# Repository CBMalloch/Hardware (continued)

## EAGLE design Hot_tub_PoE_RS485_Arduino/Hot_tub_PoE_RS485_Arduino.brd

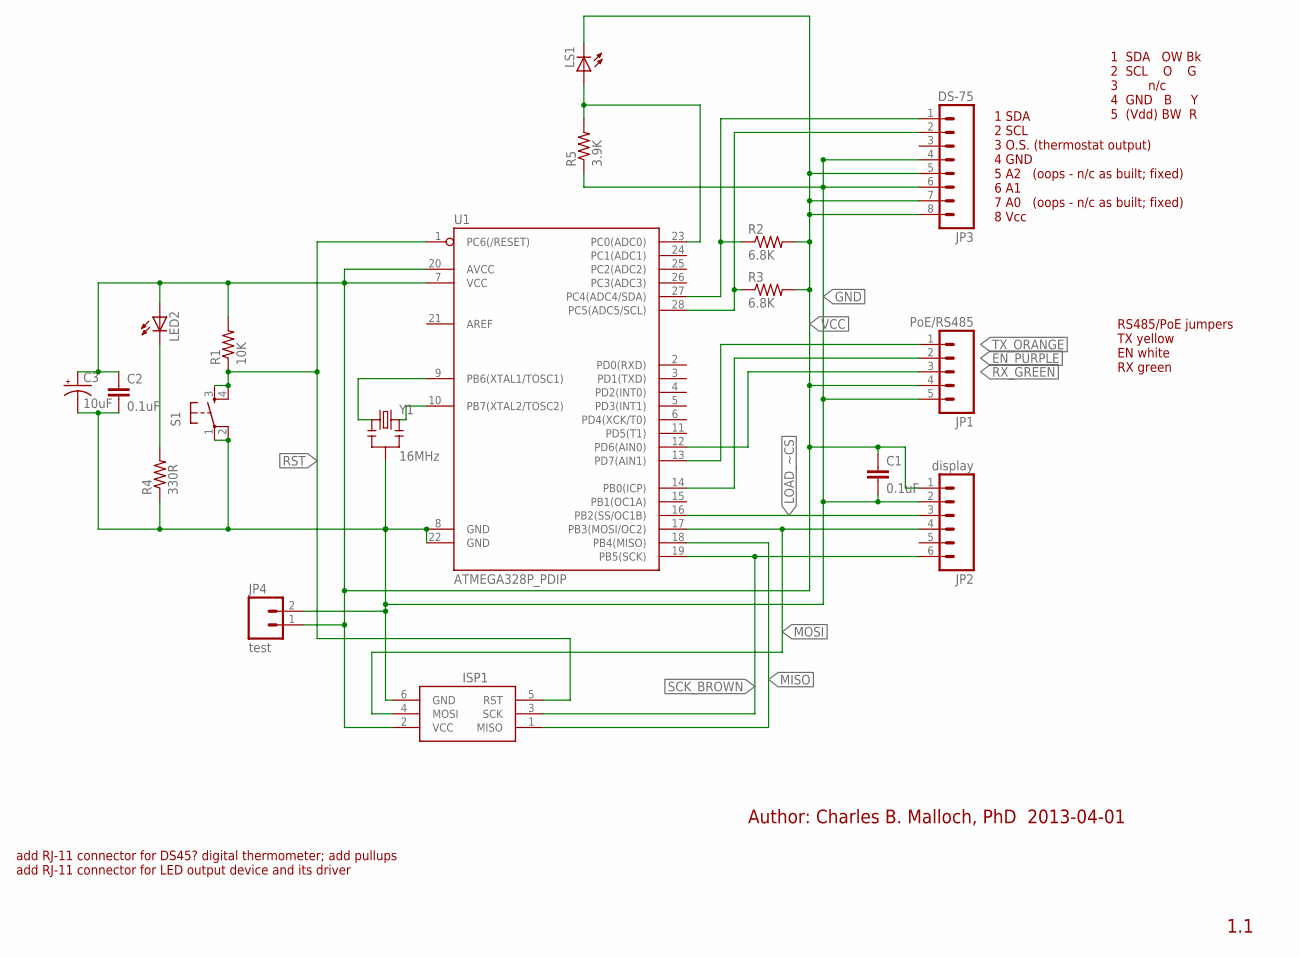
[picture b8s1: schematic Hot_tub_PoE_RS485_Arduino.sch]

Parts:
C1, C2: 0.1uF; CAP-PTH-SMALL
C3: 10uF; CPOL-RADIAL-10UF-25V
ISP1: AVRISP-6; AVRISP
JP1: PoE/RS485; 1X05_LOCK_LONGPADS
JP2: display; 1X06_LOCK_LONGPADS
JP3: DS-75; 1X08_LOCK_LONGPADS
JP4: test; 1X02_LOCK_LONGPADS
LED2: LED5MM
LS1: LED5MM
R1: 10K; 0204/5
R2, R3: 6.8K; 0207/10
R4: 330R; 0207/10
R5: 3.9K; 0207/10
S1: TAC_SWITCHPTH; TACTILE-PTH
U1: ATMEGA328P_PDIP; DIL28-3
Y1: 16MHz; RESONATOR-PTH

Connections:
EN_PURPLE: JP1.2, U1.14 (PB0(ICP))
GND: C1.2, C2.2, C3.2 (-), ISP1.6 (GND), JP1.5, JP2.2, JP3.4, JP3.6, JP4.2, R4.1, R5.1, S1.1, S1.2, U1.8 (GND), U1.22 (GND), Y1.2
LOAD_~CS: JP2.3, U1.16 (PB2(SS/OC1B))
MISO: ISP1.1 (MISO), U1.18 (PB4(MISO))
MOSI: ISP1.4 (MOSI), JP2.4, U1.17 (PB3(MOSI/OC2))
unnamed: JP3.1, R2.1, U1.27 (PC4(ADC4/SDA))
unnamed: LED2.K (C), R4.2
unnamed: LS1.A, R5.2, U1.23 (PC0(ADC0))
unnamed: U1.10 (PB7(XTAL2/TOSC2)), Y1.3
unnamed: JP3.2, R3.1, U1.28 (PC5(ADC5/SCL))
unnamed: U1.9 (PB6(XTAL1/TOSC1)), Y1.1
RST: ISP1.5 (RST), R1.1, S1.3, S1.4, U1.1 (PC6(/RESET))
RX_GREEN: JP1.3, U1.12 (PD6(AIN0))
SCK_BROWN: ISP1.3 (SCK), JP2.6, U1.19 (PB5(SCK))
TX_ORANGE: JP1.1, U1.13 (PD7(AIN1))
VCC: C1.1, C2.1, C3.1 (+), ISP1.2 (VCC), JP1.4, JP2.1, JP3.5, JP3.7, JP3.8, JP4.1, LED2.A, LS1.K (C), R1.2, R2.2, R3.2, U1.7 (VCC), U1.20 (AVCC)

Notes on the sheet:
Author: Charles B. Malloch, PhD 2013-04-01
1.1
add RJ-11 connector for DS45? digital thermometer; add pullups add RJ-11 connector for LED output device and its driver
1 SDA 2 SCL 3 O.S. (thermostat output) 4 GND 5 A2 (oops - n/c as built; fixed) 6 A1 7 A0 (oops - n/c as built; fixed) 8 Vcc
1 SDA OW Bk 2 SCL O G 3 n/c 4 GND B Y 5 (Vdd) BW R
RS485/PoE jumpers TX yellow EN white RX green

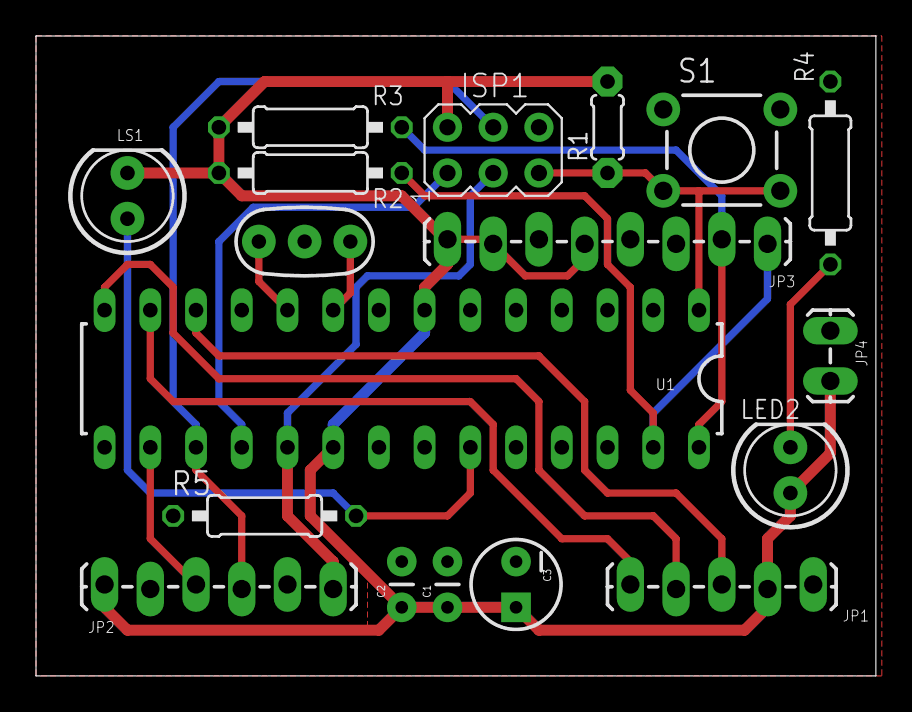
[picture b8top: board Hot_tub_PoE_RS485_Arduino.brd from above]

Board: 2 copper layers, 46.7 x 35.5 mm, 18 parts (0 on the bottom side), 16 nets.

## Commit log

2013-11-26 EMMA5 bus interfaces, first push
    Ready to go
2014-02-03 Initial add of hot tub monitor boards
2014-02-03 added LED_Display
2014-03-10 Hot tub fill monitor: added
    other updates
2016-03-03 create ESP8266 daughter board
    ESP8266 daughter board for ESP-01
2017-11-13 Preamplifier for piezo audio sensor
    I have a Cricket violin, an inexpensive travel-style violin made by the Magic Fluke company. It has a piezoelectric element atop the soundpost. The piezo is a very high impedance device, generating s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
2018-04-04 Re-laid boards for smaller real estate, converted to all SMD
2018-04-04 Update DESCRIPTION
2019-03-21 Board, schematic, and Gerbers for ATtiny Development Board
    initial submission
2019-03-21 added pdfs
